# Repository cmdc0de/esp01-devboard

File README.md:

# esp01-devboard
development board for esp8266 (esp01)

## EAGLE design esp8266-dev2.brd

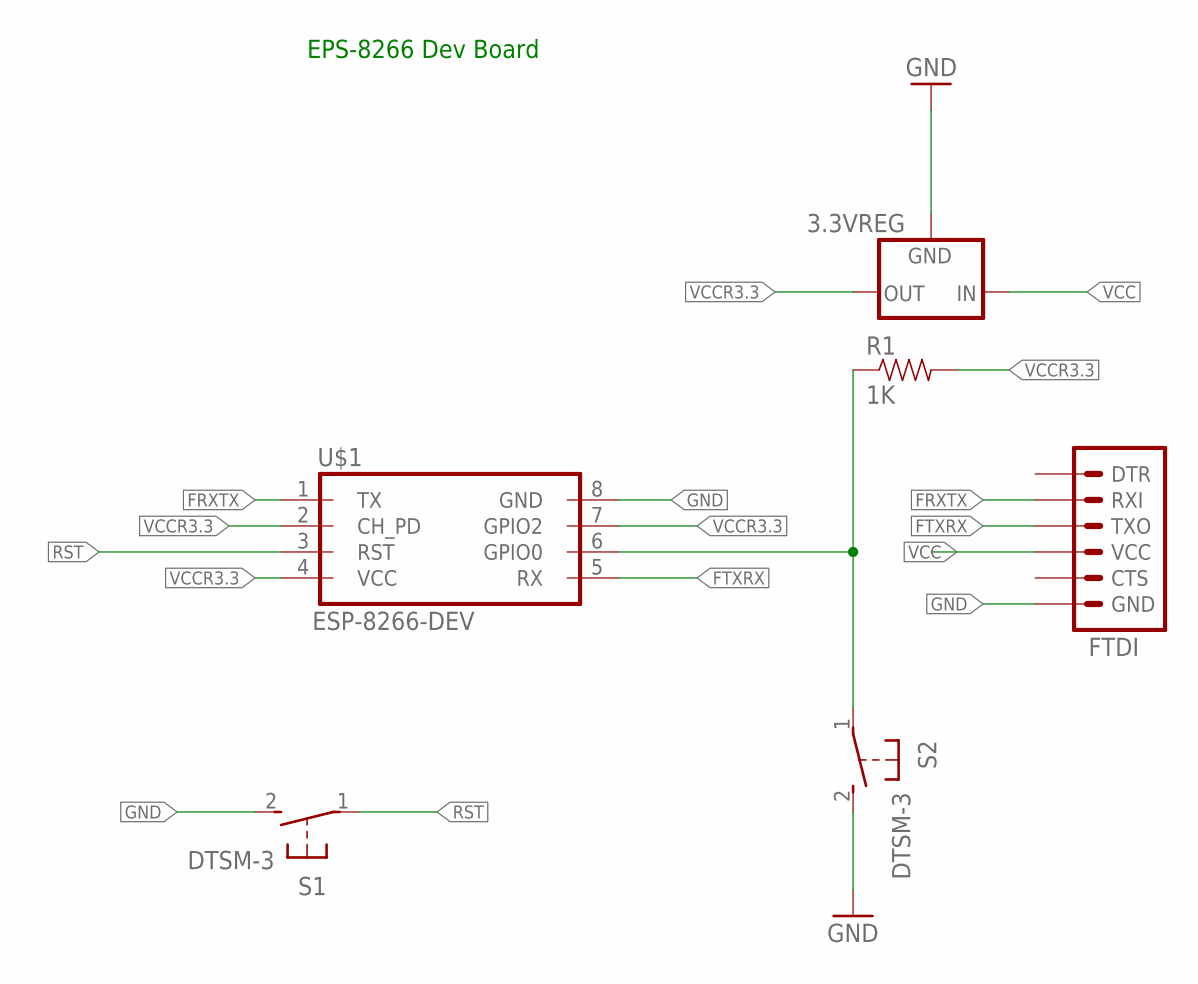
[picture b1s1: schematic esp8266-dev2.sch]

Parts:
3.3VREG: LM1117V; 78XXS
FTDI: ARDUINO_SERIAL_PROGRAMPTH; 1X06
R1: 1K; AXIAL-0.3EZ; MPN MCF 0.25W 1K
S1, S2: DTSM-3; MPN DTSM-32S-B
U$1: ESP-8266-DEV; 2X4

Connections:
FRXTX: FTDI.2 (RXI), U$1.1 (TX)
FTXRX: FTDI.3 (TXO), U$1.5 (RX)
GND: 3.3VREG.GND, FTDI.6 (GND), S1.2, S2.2, U$1.8 (GND)
unnamed: R1.P$1 (1), S2.1, U$1.6 (GPIO0)
RST: S1.1, U$1.3 (RST)
VCC: 3.3VREG.IN, FTDI.4 (VCC)
VCCR3.3: 3.3VREG.OUT, R1.P$2 (2), U$1.2 (CH_PD), U$1.4 (VCC), U$1.7 (GPIO2)

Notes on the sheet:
EPS-8266 Dev Board

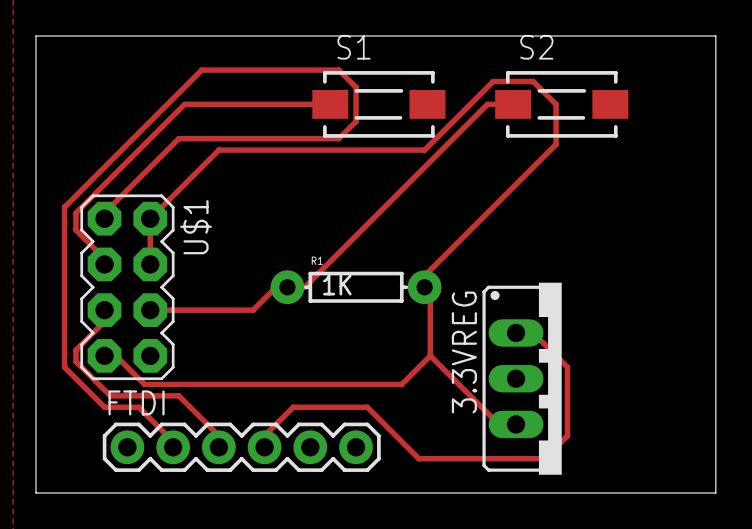
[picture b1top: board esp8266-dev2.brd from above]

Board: 2 copper layers, 37.8 x 25.4 mm, 6 parts (0 on the bottom side), 7 nets.

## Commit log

2016-09-26 initial files

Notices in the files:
parts and their libraries:
SparkFun-Connectors: Licensing: Creative Commons ShareAlike 4.0 International - https://creativecommons.org/licenses/by-sa/4.0
